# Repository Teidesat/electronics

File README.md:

# Hardware de TeideSat

En este repositorio se encuentra todo lo relacionado con la electrónica que va a llevar el nanosatélite TEIDESAT-I

Dentro de este repositorio se colocarán todos los proyectos e información que se necesite para desarrollar el hardware.

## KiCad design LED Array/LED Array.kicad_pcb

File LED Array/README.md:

# Matriz LED para la payload
El objetivo de este proyecto es investigar el funcionamiento de una matriz de LEDs que sustituya los cuatro LEDs que se utilizan actualmente.

- Ventajas:
  - Mayor control sobre cada uno de los LEDs.
  - Posiblidad de menor consumo.
  - Mayor redundancia y fiabilidad.
- Inconvenientes:
  - Mayor complejidad.
  - Hardware más específico para controlar todos los LEDs.

---
## Versiones:
### V0.1: Break it!
Matriz LED de 5x5 con un socket estándar, tipo Arduino/ESP32.
##### Objetivo: 
Comprobar el funcionamiento de una matriz de LEDs, sus limitaciones y llevar los componentes al punto de ruptura.
##### Análisis a realizar:
- [ ] Curva característica de los LEDs.
- [ ] Punto de ruptura de los LEDs.
- [ ] Velocidad de parpadeo.
- [ ] Detección de mensajes básicos con receptores ópticos.

##### Resultados:
TBD.

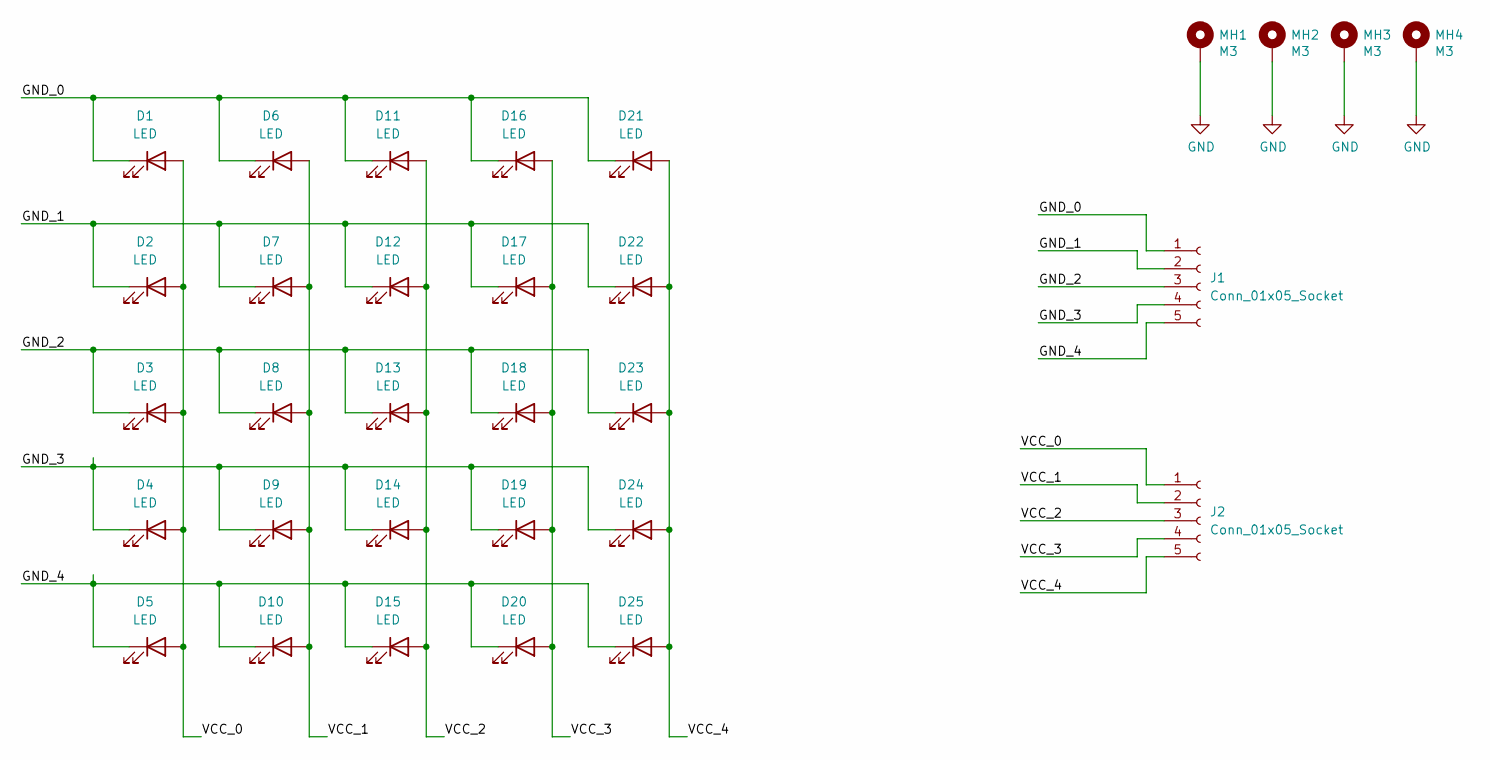
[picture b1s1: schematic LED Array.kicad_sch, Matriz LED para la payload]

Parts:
D1, D2, D3, D4, D5, D6, D7, D8, D9, D10, D11, D12, D13, D14, D15, D16, D17, D18, D19, D20, D21, D22, D23, D24, D25: LED; SM5730UWDW05
J1, J2: Conn_01x05_Socket; PinSocket_1x05_P2.54mm_Vertical
MH1, MH2, MH3, MH4: M3; MountingHole_3.2mm_M3_Pad

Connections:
/GND_0: D1.1 (K), D6.1 (K), D11.1 (K), D16.1 (K), D21.1 (K), J1.1
/GND_1: D2.1 (K), D7.1 (K), D12.1 (K), D17.1 (K), D22.1 (K), J1.2
/GND_2: D3.1 (K), D8.1 (K), D13.1 (K), D18.1 (K), D23.1 (K), J1.3
/GND_3: D4.1 (K), D9.1 (K), D14.1 (K), D19.1 (K), D24.1 (K), J1.4
/GND_4: D5.1 (K), D10.1 (K), D15.1 (K), D20.1 (K), D25.1 (K), J1.5
/VCC_0: D1.2 (A), D2.2 (A), D3.2 (A), D4.2 (A), D5.2 (A), J2.1
/VCC_1: D6.2 (A), D7.2 (A), D8.2 (A), D9.2 (A), D10.2 (A), J2.2
/VCC_2: D11.2 (A), D12.2 (A), D13.2 (A), D14.2 (A), D15.2 (A), J2.3
/VCC_3: D16.2 (A), D17.2 (A), D18.2 (A), D19.2 (A), D20.2 (A), J2.4
/VCC_4: D21.2 (A), D22.2 (A), D23.2 (A), D24.2 (A), D25.2 (A), J2.5
GND: MH1.1, MH2.1, MH3.1, MH4.1

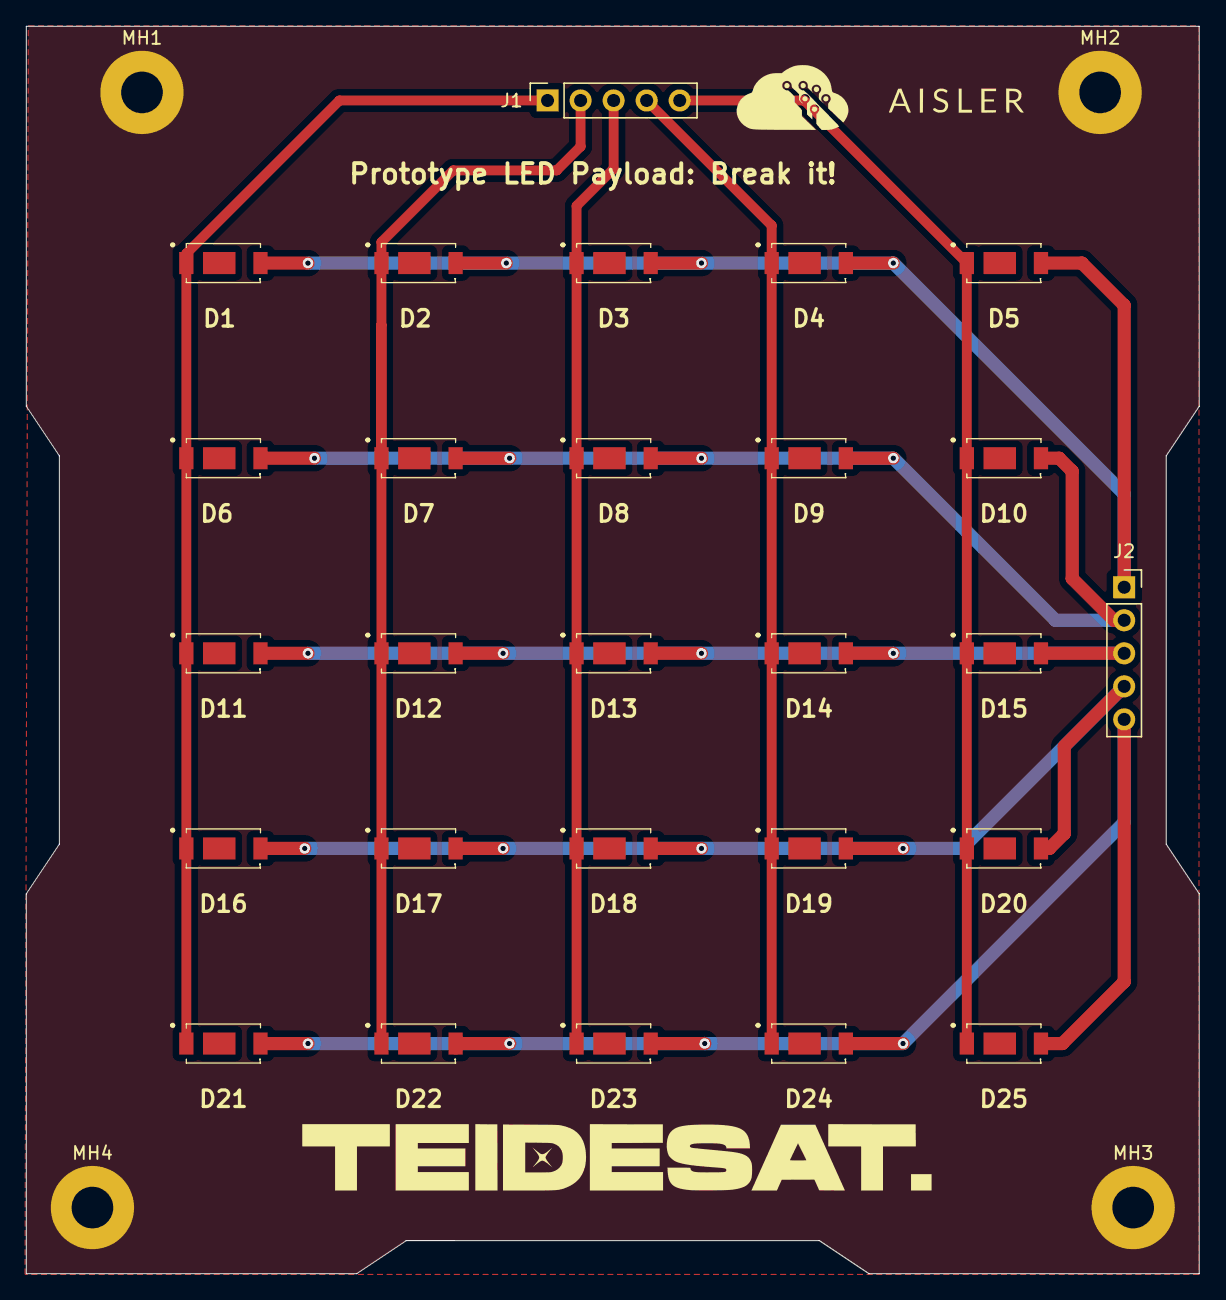
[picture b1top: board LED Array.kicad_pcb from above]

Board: 2 copper layers, 90.2 x 95.9 mm, 31 parts (0 on the bottom side), 11 nets.

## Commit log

2024-04-09 Versión inicial
2024-04-09 V0.1 LED Array
